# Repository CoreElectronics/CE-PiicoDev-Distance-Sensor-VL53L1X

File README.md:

# PiicoDev Distance Sensor VL53L1X

This is the repo for the [PiicoDev® Distance Sensor](https://core-electronics.com.au/catalog/product/view/sku/CE07741) PCB.

The PiicoDev® Distance Sensor is a long-distance laser-ranging sensor that uses Time-of-Flight (ToF) to accurately measure distances up to 4m.

- Small size, millimetre precision
- Can be protected behind many cover-window materials.
- PiicoDev connector, compatible with Qwiic and STEMMA QT (3.3V only)
- 2.54mm breakout for breadboarding/prototyping
- Manufactured and [supported](https://core-electronics.com.au/contacts/) in Australia by Core Electronics

# License
This project is open source - please review the LICENSE.md file for further licensing information.

If you have any technical questions, or concerns about licensing, please contact technical support on the [Core Electronics forums](https://forum.core-electronics.com.au/).

# Attribution
The hardware design of this module is influenced by the design from Sparkfun ([repo](https://github.com/sparkfun/Qwiic_Distance_VL53L1X)).

*\"PiicoDev\" and the PiicoDev logo are trademarks of Core Electronics Pty Ltd.*

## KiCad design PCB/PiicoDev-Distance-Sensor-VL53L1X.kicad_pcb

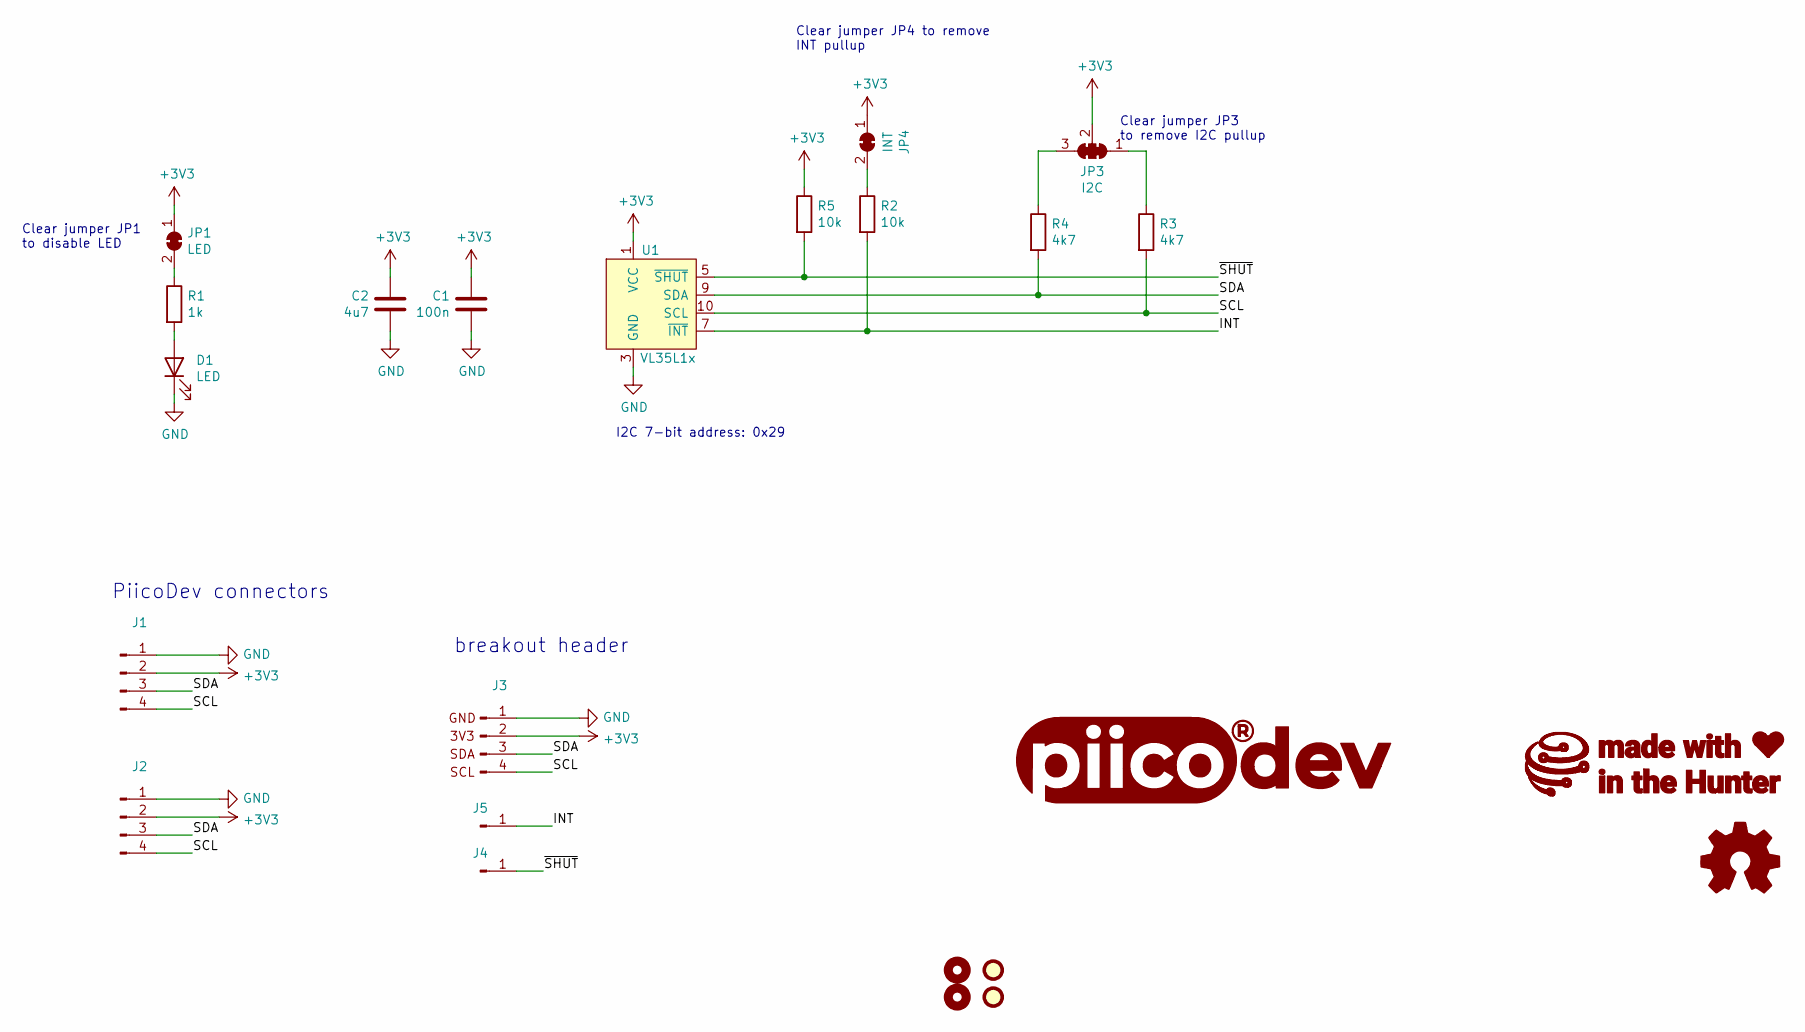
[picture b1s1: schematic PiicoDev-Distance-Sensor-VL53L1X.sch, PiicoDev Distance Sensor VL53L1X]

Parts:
C1: 100n; C_0402_1005Metric
C2: 4u7; C_0402_1005Metric
D1: LED; LED_0603_1608Metric
FID1, FID2: Fiducial; Fiducial_1mm_Mask2mm
G1: LOGO_CoreElectronics_made-with-love; piicodev_logo_14.2x3.4mm
G2: LOGO_piico; piicodev_logo_14.2x3.4mm
H1, H4: MountingHole; MountingHole_2.7mm_M2.5
J1, J2: JST_SH_SM04B-SRSS-TB_1x04-1MP_P1.00mm_Horizontal
J3: PiicoDev_header_4pin
J4: PinHeader_1x01_P2.54mm_Vertical
J5: PiicoDev_header_1pin_INT_uninverted
JP1: LED; SolderJumper-2_P1.3mm_Bridged_RoundedPad1.0x1.5mm
JP3: I2C; SolderJumper-3_P1.3mm_Closed_RoundedPad1.0x1.5mm_NumberLabe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
JP4: INT; SolderJumper-2_P1.3mm_Bridged_RoundedPad1.0x1.5mm
LOGO1: Logo_Open_Hardware_Small; oshw
R1: 1k; R_0402_1005Metric
R2, R5: 10k; R_0402_1005Metric
R3, R4: 4k7; R_0402_1005Metric
U1: VL35L1x; ST_VL53L1X

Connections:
+3V3: C1.2, C2.2, J1.2, J2.2, J3.2, JP1.1 (A), JP3.2 (C), JP4.1 (A), R5.1, U1.1 (VCC), U1.11 (VCC)
/INT: J5.1, R2.2, U1.7 (~INT)
/SCL: J1.4, J2.4, J3.4, R3.2, U1.10 (SCL)
/SDA: J1.3, J2.3, J3.3, R4.2, U1.9 (SDA)
/~SHUT: J4.1, R5.2, U1.5 (~SHUT)
GND: C1.1, C2.1, D1.1 (K), J1.1, J2.1, J3.1, U1.2 (GND), U1.3 (GND), U1.4 (GND), U1.6 (GND), U1.12 (GND)
unnamed: D1.2 (A), R1.2
unnamed: JP1.2 (B), R1.1
unnamed: JP3.1 (A), R3.1
unnamed: JP3.3 (B), R4.1
unnamed: JP4.2 (B), R2.1

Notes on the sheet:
Clear jumper JP1 to disable LED
Clear jumper JP3 to remove I2C pullup
PiicoDev connectors
breakout header
I2C 7-bit address: 0x29
Clear jumper JP4 to remove INT pullup

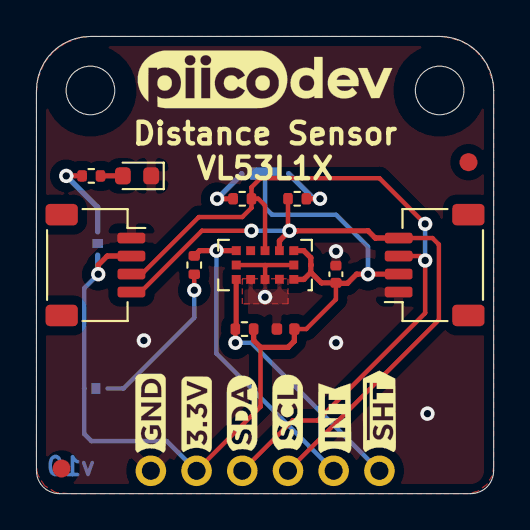
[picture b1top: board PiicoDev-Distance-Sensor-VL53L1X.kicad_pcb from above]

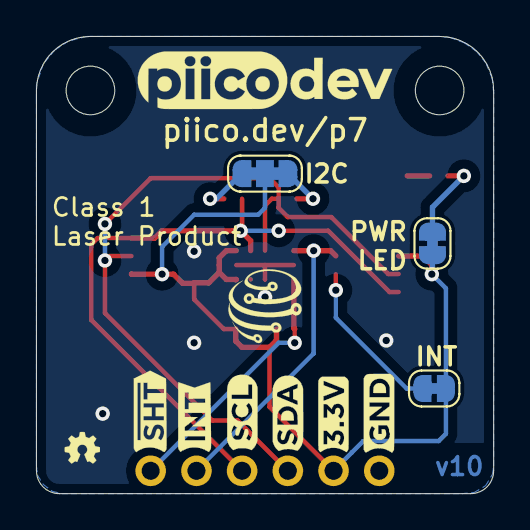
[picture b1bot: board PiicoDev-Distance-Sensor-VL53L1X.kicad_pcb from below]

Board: 2 copper layers, 25.4 x 25.4 mm, 24 parts (7 on the bottom side), 11 nets.

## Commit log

2021-11-16 Update resistor values - all 10k

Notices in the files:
PCB/PiicoDev-Distance-Sensor-VL53L1X.sch:
License: CCASAv4.0 http://creativecommons.org/licenses/by-sa/4.0
